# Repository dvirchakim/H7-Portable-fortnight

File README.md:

# Flight-controller carrier for Arduino® Portenta H7

**A 68 × 40 mm, 4-layer carrier that snaps onto the Portenta H7's two high-density connectors and turns it
into an ArduPilot-class flight controller**, with Pixhawk-standard ports, microSD logging and DroneCAN.

**Revision R0.4 · fab-ready, not yet built.** DRC and ERC clean, 0 JLCDFM-style dangers, schematic and PCB
agree pad for pad, sockets match Arduino's own Portenta Breakout to 0.000 mm.

## Highlights

- **Power:** 3–6S LiPo in, TI LMR33630 buck, 5.25 V at 2 A continuous (1.5 A from 3S), 3 A peaks.
- **Sensors:** TDK ICM-45686 IMU at the board centre, Bosch BMP581 barometer shielded under the module.
- **Logging and buses:** 4-bit microSD, DroneCAN (terminated by default), I2C.
- **Ports:** GPS, TELEM (with flow control), RC, UART, CAN and I2C on JST-GH with Pixhawk DS-009
  pinouts; 4-in-1 ESC on JST-SH 8 in the Betaflight standard order.
- **Motors:** DShot and bidirectional DShot on all four; ESC telemetry on its own UART.
- **Measurement:** battery voltage and ESC current into an ADC with its own 2.5 V reference.
- **Mounting:** 30.5 mm M3 stack pattern; the module is held by its own four M2 holes.
- **Built from code:** everything is generated from one Python netlist (`scripts/design.py`) and
  checked by scripts: DRC, ERC, DFM, EMI, socket match, JLCPCB placement.

## Specifications

| | |
|---|---|
| Board | 68 × 40 mm, 4 layers (GND and 5 V planes), 1.6 mm, black mask / white silk, ENIG |
| Module | Portenta H7 / H7 Lite (STM32H747, M7 480 MHz + M4) on two Hirose DF40HC(3.5), 3.5 mm stack |
| Input | 3–6S LiPo through solder pads or the ESC harness; SMBJ26A TVS |
| Outputs | M1–M4 (DShot), S5, S6, WS2812 LED strip, buzzer |
| Parts | 63 placed parts, 32 BOM lines; about $22 per board in parts at 10 boards (module not included) |
| Assembly | JLCPCB, both sides; the DF40 sockets are consigned |

## Architecture

| Block | Parts | H7 signals |
|---|---|---|
| Power | 3-6S VBAT -> TVS -> LMR33630 buck 5.25 V (2 A continuous from 4-6S, ~1.5 A from 3S, 3 A peaks) -> SS34 -> +5V -> H7 VIN | J1-21/32/41/48 |
| Sensor rail | LP5907 3.3 V low-noise LDO from +5V | — |
| IMU | TDK ICM-45686, SPI | SPI1 CK/CIPO/COPI (PI1/PC2/PC3), CS PI0, INT GPIO2 (PD4) |
| Barometer | Bosch BMP581 (I2C, address 0x46) | I2C0 (PH8/PH7 = I2C3) |
| Magnetometer | LIS3MDL footprint, not fitted — use the GPS module's compass | I2C0 |
| Motors M1-M4 | 8-pin JST-SH 4-in-1 ESC connector (Betaflight standard order) | M1 PWM5 PK1 TIM1_CH1, M2 PWM4 PJ11 TIM1_CH2, M3 PWM1 PC6 TIM3_CH1, M4 PWM2 PC7 TIM3_CH2: no complementary channels, DMA on both timers, so DShot and bidirectional DShot work on all four |
| Aux S5, S6, LED strip | pads | LED strip PWM8 PJ10 = TIM8_CH2 (has DMA, so WS2812 works); S6 PWM6 PH15 = TIM8_CH3N (shares TIM8 with the LEDs: second LED string or GPIO while they run); S5 PWM9 PH6 = TIM12_CH1 (servo PWM) |
| Buzzer | 2N7002 low-side switch (R13 100k), pad | PWM7 PJ7 as a GPIO: active buzzer |
| Status / power LEDs | red (GPIO3) / white (+5V) | GPIO3 PD5 |
| Battery sense | VBAT 11:1 divider -> A6; ESC current (10k + 100 nF) -> A7; ADC VREF+ = 2.5 V from a TI REF3125 (U7) | A6 PA4 J2-78, A7 PA6 J2-80, VREF+ J2-71 (VREF- J2-72 to GND) |
| GPS + compass | JST-GH 6 (5V TX RX SCL SDA GND) | UART0 + I2C0 |
| Telemetry | JST-GH 6 with RTS/CTS | UART1 (USART1) |
| RC receiver | JST-GH 4 | UART2 (USART6) |
| Spare UART | JST-GH 4 | UART3 (UART8) |
| ESC telemetry | J10 pin 4 | PA8 = UART7_RX (J2-59), its own UART (the module's Bluetooth UART: keep Bluetooth off) |
| CAN | SN65HVD230 + JST-GH 4; 120 ohm terminator ON by default (bridged JP1: cut to remove) | CAN1 TX/RX (PH13/PB8) = FDCAN1 |
| I2C expansion | JST-GH 4 | I2C0 |
| microSD | Molex 104031-0811 | SDC (SDMMC2) |
| Debug | SWDIO/SWCLK/NRST/GND/3V3 pads (bottom) | J1-75/77/73 |

The +5V rail sits after the Schottky, on the same node as the H7's VIN, so the sensors and ports
run from USB on the bench and USB cannot back-feed the buck.

## Snap-on interface

- Carrier sockets J1/J2: **Hirose DF40HC(3.5)-80DS-0.4V(51)**, mating the H7's DF40C-80DP-0.4V(51).
  Board-to-board gap 3.5 mm.
- J1/J2 are 43.18 mm apart on the H7 centreline (17.14 mm and 60.32 mm from the USB edge).
- Pin 1, seen from the top with USB on the left: J1 pin 1 is in the USB-side row at the lower end;
  J2 pin 1 is in the outer row at the upper end. Same as Arduino's Portenta Breakout
  (`scripts/check_sockets.py`).
- Four M2 holes line up with the H7's corner holes — use 3.5 mm spacers so vibration is not
  carried by the connectors. At the J2 end use round spacers of 3 mm diameter or less.
- Four M3 holes on the standard 30.5 x 30.5 mm stack pattern.
- Under the H7 the top side carries only low parts (LGA sensors, 0402). Everything tall (buck,
  inductor, microSD, CAN transceiver) is on the bottom.

## Documentation

| Topic | What's there |
|---|---|
| [Rev 0.4 changes](docs/rev-0.4/README.md) | Sensor cost pass: BMP581 barometer; IMU options checked |
| [Rev 0.3 changes](docs/rev-0.3/README.md) | The design review: what was found and fixed, what's left for rev 0.4 |
| [Rev 0.2 changes](docs/rev-0.2/README.md) | Re-route, buck loop, EMI ring, cost pass, sensor swap |
| [Verification](docs/verification/README.md) | The "must verify before ordering" checks with results, and the bring-up / production test |
| [Ordering](docs/ordering/README.md) | What to upload to JLCPCB, stackup, consigning the DF40 sockets |
| [BOM and cost](docs/bom-and-cost/README.md) | Cost per board and why each main part was chosen |
| [Placement check](docs/placement-check/README.md) | JLCPCB footprint corrections and what they caught |
| [DFM](docs/dfm/README.md) | JLCDFM-style manufacturability results |
| [EMI](docs/emi/README.md) | Layout checks and the bench test procedure |
| [Routing](docs/routing/README.md) | Layer stack and the routing flow |
| [Silkscreen](docs/silkscreen/README.md) | Labels, forward arrows, QR code |
| [Firmware](docs/firmware/README.md) | The ArduPilot port: what the board definition needs |
| [Design review page](docs/FC_Carrier_R0.3_review.html) | The rev 0.3 review written for an Arduino Pro pitch |

## Repository layout

| File | What |
|---|---|
| `portenta_drone_fc.kicad_pro` | Open this in KiCad 7 |
| `portenta_drone_fc.kicad_sch` | Schematic (net-label style, one sheet) |
| `portenta_drone_fc.kicad_pcb` | Routed 4-layer board |
| `fc.pretty/`, `fc.kicad_sym` | Project footprint (DF40 socket) and symbols |
| `bom_placement.csv` | Parts, MPNs, side and XY (from `design.py`) |
| `fab/` | Gerber zip, JLCPCB BOM and CPL, `bom_cost.csv`, `placement_check.csv` |
| `out/` | Renders, `drc.rpt`, `dfm.rpt`, `emi.rpt` |
| `docs/` | One folder per topic (see Documentation above), the 3D renders, `portenta_breakout_sockets.json` (Arduino's socket pads) and `FC_Carrier_R0.3_review.html` (the rev 0.3 design review for the Arduino pitch) |
| `scripts/design.py` | **Single source of truth** — parts, nets, placement |
| `scripts/regen_docs.py` | Rewrites schematic + BOM CSV from `design.py` without touching the routed board |
| `scripts/check_sockets.py` | Compares J1/J2 pad by pad with Arduino's Portenta Breakout and Hirose's land pattern / hatched area (exit 0 = match) |
| `scripts/erc.py` | ERC for the generated schematic plus schematic-vs-PCB parity, pad by pad (exit 0 = clean) |
| `scripts/power_copper.py` | Thermal vias in U1's exposed pad and power tracks widened as far as clearance allows |
| `scripts/render3d/` | Headless 3D renders of the board (STEP export -> blocks, layer textures, Blender) |
| `scripts/r03_renet.py`, `scripts/r03_rip.py` | The rev 0.3 review changes as applied to the routed board: net swaps, pad re-assignments, new footprints, then removal of the obsolete copper (run once; kept as the record) |
| `scripts/altium_pads.py` | Reads pads/nets from an Altium `.PcbDoc` with plain Python (made the reference JSON) |

`scripts/gen.py --force` would regenerate the board and discard the routing — do not use it now.

---

Arduino® and Portenta are trademarks of Arduino S.r.l. / Arduino SA. This is an independent design, not an
Arduino product.

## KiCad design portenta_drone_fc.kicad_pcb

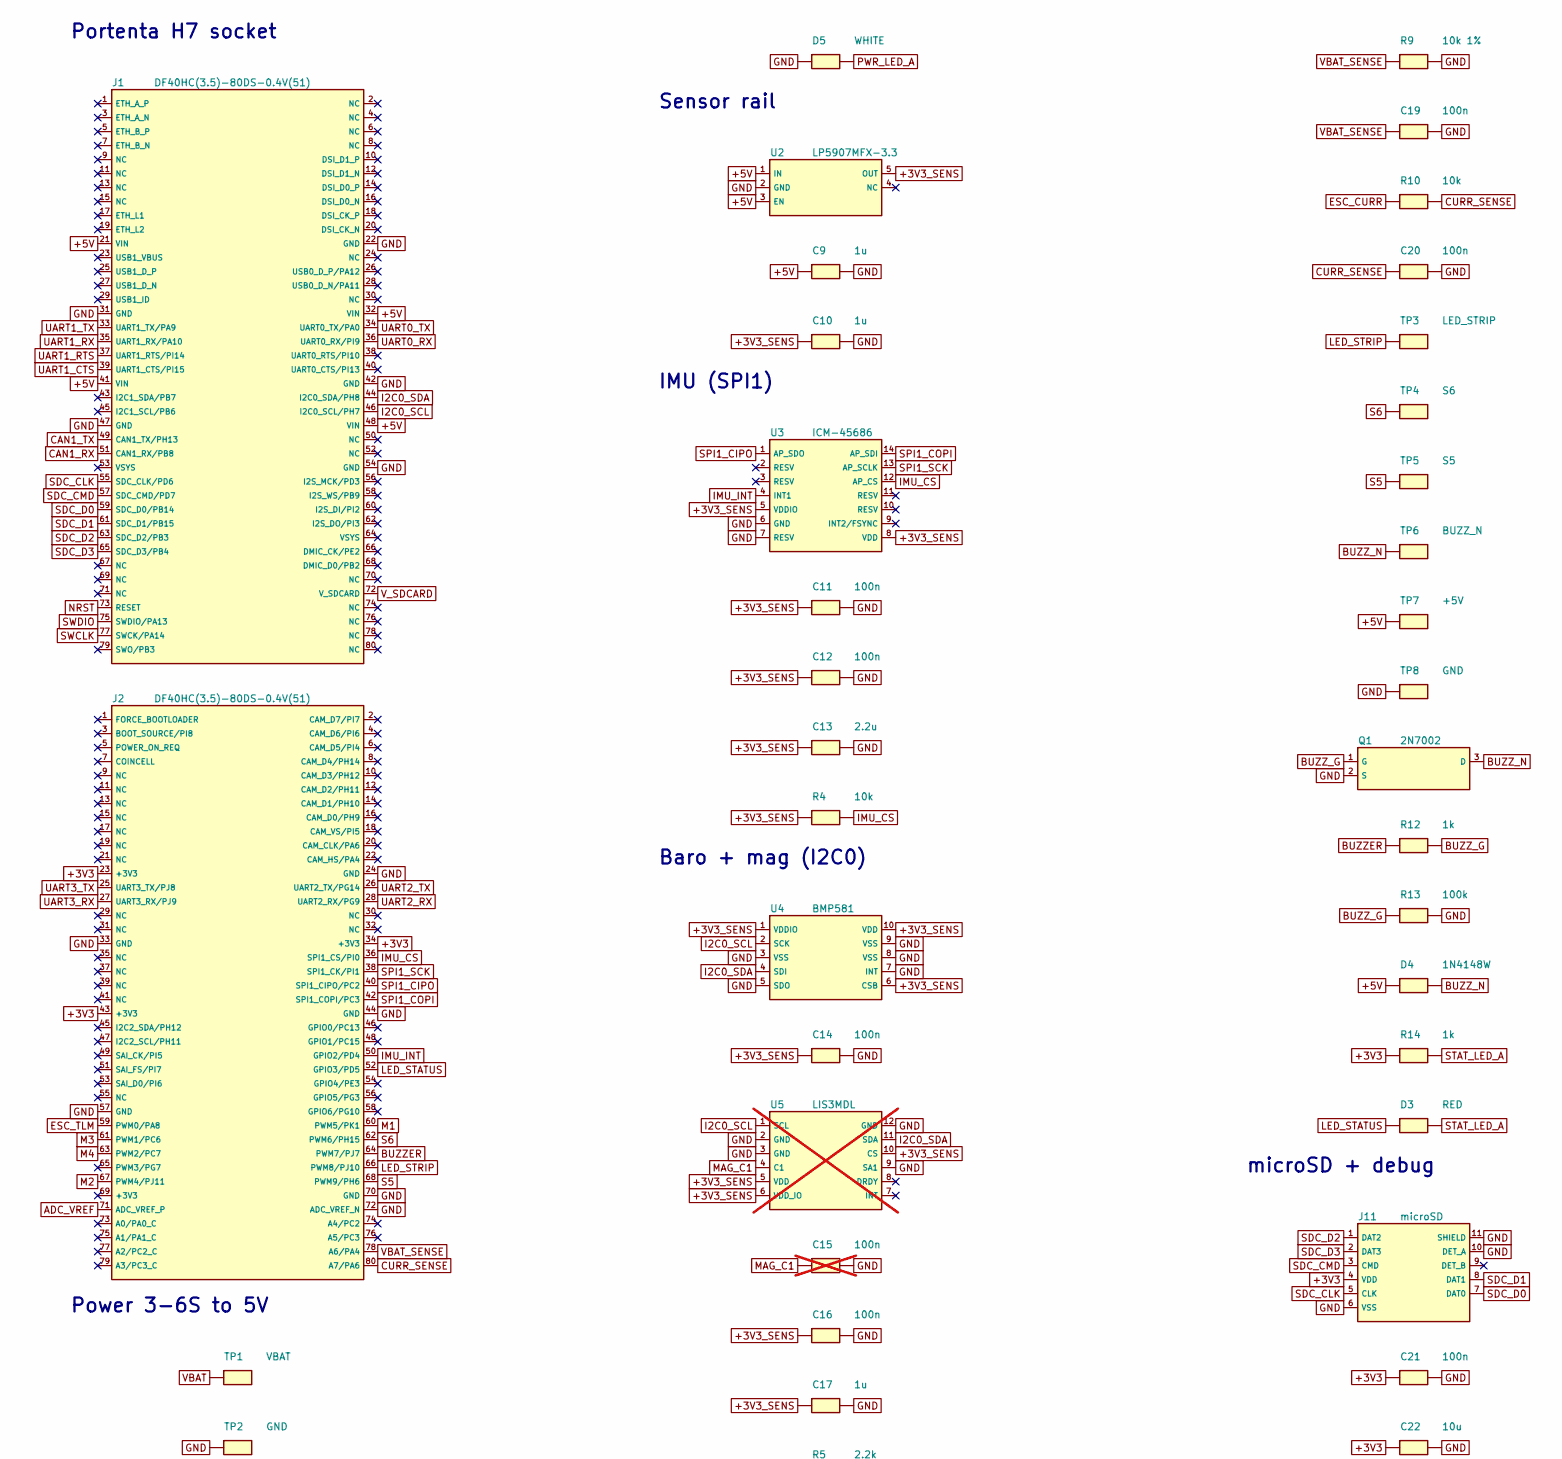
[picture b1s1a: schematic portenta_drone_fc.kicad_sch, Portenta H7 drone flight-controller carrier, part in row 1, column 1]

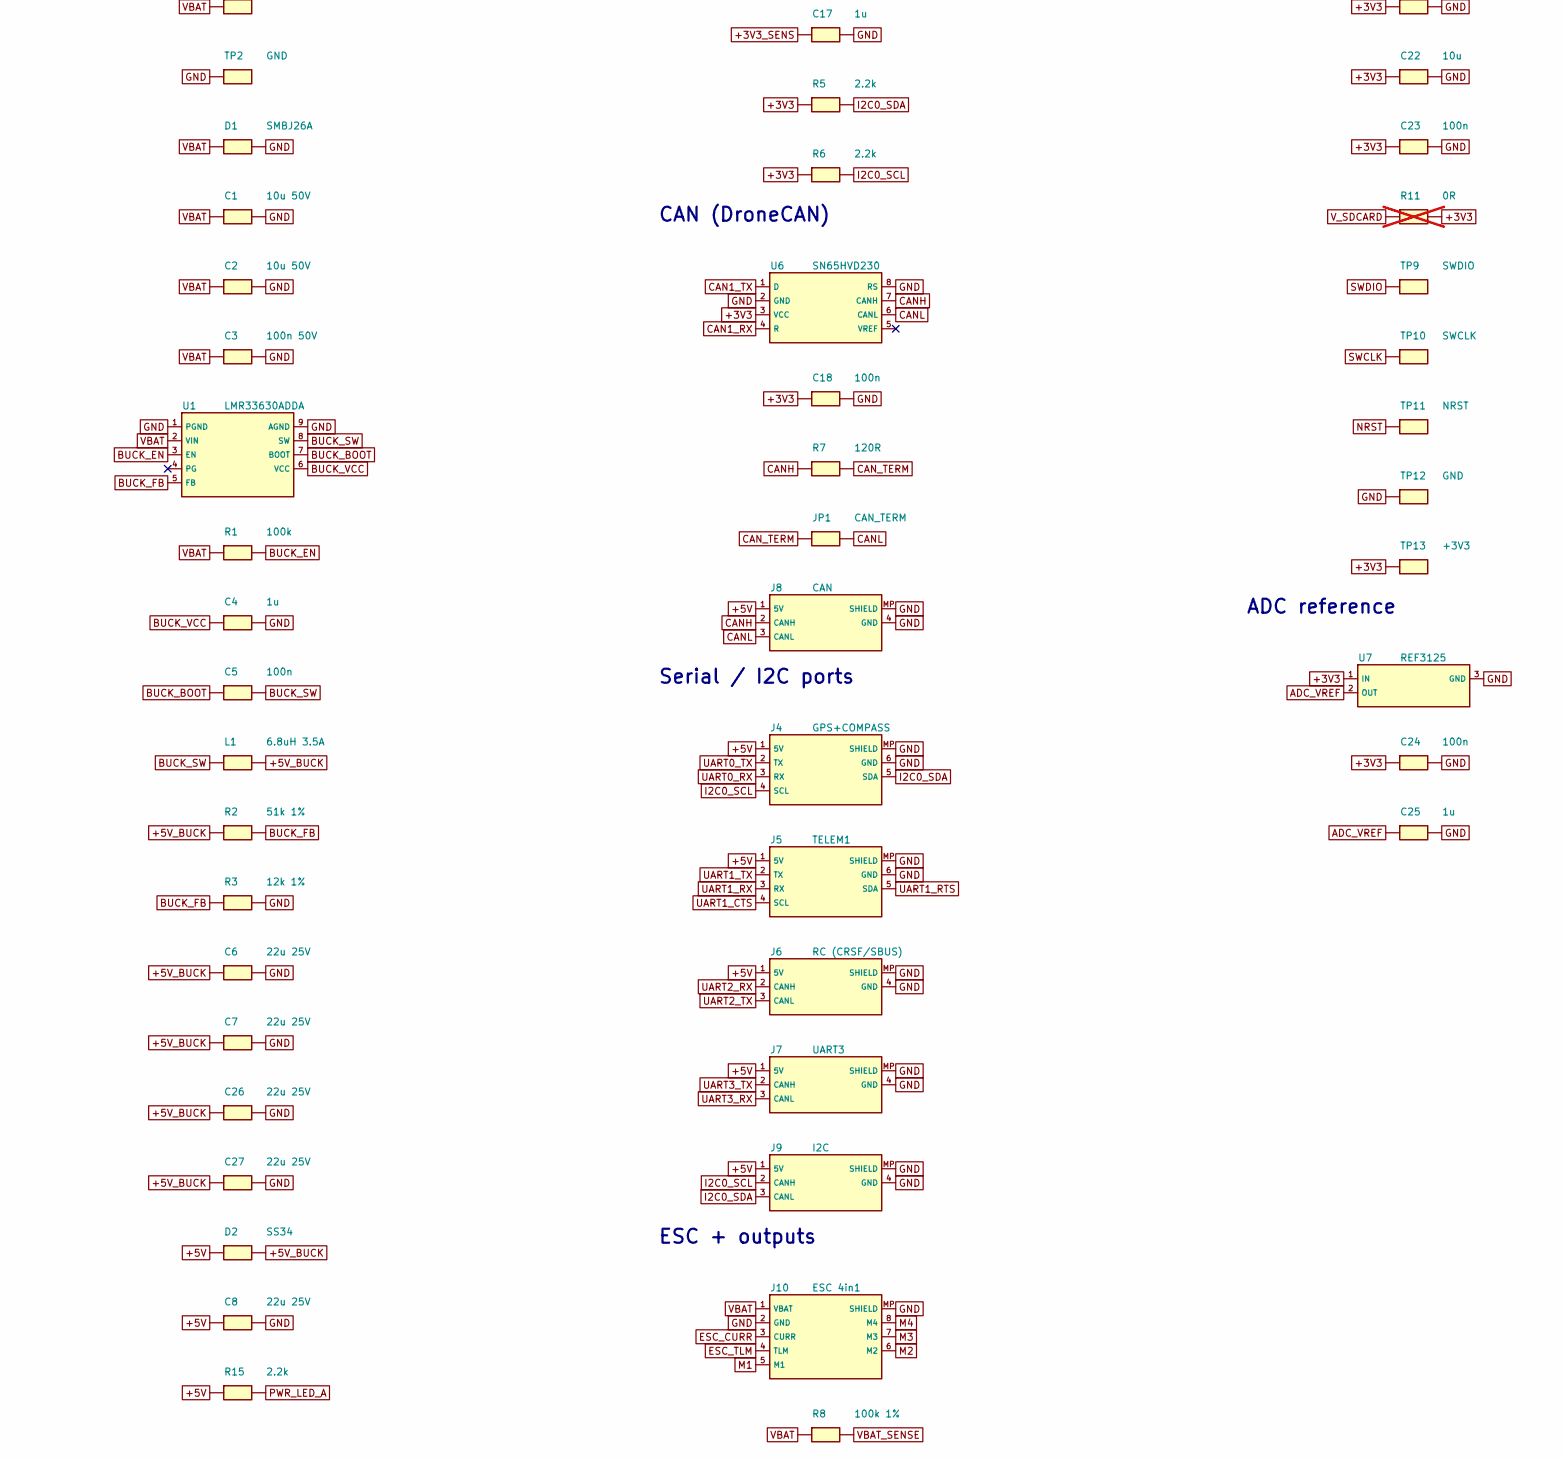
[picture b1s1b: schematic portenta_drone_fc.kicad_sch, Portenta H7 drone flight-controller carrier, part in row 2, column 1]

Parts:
C1, C2: 10u 50V; C_1206_3216Metric
C3: 100n 50V; C_0603_1608Metric
C4, C9, C10, C17, C25: 1u; C_0402_1005Metric
C5, C11, C12, C14, C16, C18, C19, C20, C21, C23, C24: 100n; C_0402_1005Metric
C6, C7, C8, C26, C27: 22u 25V; C_0805_2012Metric
C13: 2.2u; C_0402_1005Metric
C15: 100n; C_0402_1005Metric; not fitted
C22: 10u; C_0805_2012Metric
D1: SMBJ26A; D_SMB; MPN SMBJ26A
D2: SS34; D_SMA; MPN SS34
D3: RED; LED_0603_1608Metric
D4: 1N4148W; D_SOD-123; MPN 1N4148W
D5: WHITE; LED_0603_1608Metric
J1, J2: DF40HC(3.5)-80DS-0.4V(51); Hirose_DF40HC(3.5)-80DS-0.4V_2x40_P0.4mm; MPN DF40HC(3.5)-80DS-0.4V(51)
J4: GPS+COMPASS; JST_GH_SM06B-GHS-TB_1x06-1MP_P1.25mm_Horizontal
J5: TELEM1; JST_GH_SM06B-GHS-TB_1x06-1MP_P1.25mm_Horizontal
J6: RC (CRSF/SBUS); JST_GH_SM04B-GHS-TB_1x04-1MP_P1.25mm_Horizontal
J7: UART3; JST_GH_SM04B-GHS-TB_1x04-1MP_P1.25mm_Horizontal
J8: CAN; JST_GH_SM04B-GHS-TB_1x04-1MP_P1.25mm_Horizontal
J9: I2C; JST_GH_SM04B-GHS-TB_1x04-1MP_P1.25mm_Horizontal
J10: ESC 4in1; JST_SH_SM08B-SRSS-TB_1x08-1MP_P1.00mm_Horizontal
J11: microSD; microSD_HC_Molex_104031-0811; MPN 104031-0811
JP1: CAN_TERM; SolderJumper-2_P1.3mm_Bridged_RoundedPad1.0x1.5mm
L1: 6.8uH 3.5A; L_Bourns_SRP5030T; MPN MDA5030-6R8M
Q1: 2N7002; SOT-23; MPN 2N7002
R1, R13: 100k; R_0402_1005Metric
R2: 51k 1%; R_0402_1005Metric
R3: 12k 1%; R_0402_1005Metric
R4, R10: 10k; R_0402_1005Metric
R5, R6, R15: 2.2k; R_0402_1005Metric
R7: 120R; R_0402_1005Metric
R8: 100k 1%; R_0402_1005Metric
R9: 10k 1%; R_0402_1005Metric
R11: 0R; R_0402_1005Metric; not fitted
R12, R14: 1k; R_0402_1005Metric
TP1: VBAT; TestPoint_Pad_3.0x3.0mm
TP2: GND; TestPoint_Pad_3.0x3.0mm
TP3: LED_STRIP; TestPoint_Pad_1.5x1.5mm
TP4: S6; TestPoint_Pad_1.5x1.5mm
TP5: S5; TestPoint_Pad_1.5x1.5mm
TP6: BUZZ_N; TestPoint_Pad_1.5x1.5mm
TP7: +5V; TestPoint_Pad_1.5x1.5mm
TP8: GND; TestPoint_Pad_1.5x1.5mm
TP9: SWDIO; TestPoint_Pad_D1.5mm
TP10: SWCLK; TestPoint_Pad_D1.5mm
TP11: NRST; TestPoint_Pad_D1.5mm
TP12: GND; TestPoint_Pad_D1.5mm
TP13: +3V3; TestPoint_Pad_D1.5mm
U1: LMR33630ADDA; Texas_HSOP-8-1EP_3.9x4.9mm_P1.27mm; MPN LMR33630ADDAR
U2: LP5907MFX-3.3; SOT-23-5; MPN LP5907MFX-3.3/NOPB
U3: ICM-45686; LGA-14_3x2.5mm_P0.5mm_LayoutBorder3x4y; MPN ICM-45686
U4: BMP581; Bosch_LGA-10_2x2mm_P0.5mm_BMP581; MPN BMP581
U5: LIS3MDL; LGA-12_2x2mm_P0.5mm; MPN LIS3MDLTR; not fitted
U6: SN65HVD230; SOIC-8_3.9x4.9mm_P1.27mm; MPN SN65HVD230DR
U7: REF3125; SOT-23; MPN REF3125AIDBZR

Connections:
+3V3: C18.1, C21.1, C22.1, C23.1, C24.1, J2.23 (+3V3), J2.34 (+3V3), J2.43 (+3V3), J11.4 (VDD), R5.1, R6.1, R11.2, R14.1, TP13.1, U6.3 (VCC), U7.1 (IN)
+3V3_SENS: C10.1, C11.1, C12.1, C13.1, C14.1, C16.1, C17.1, R4.1, U2.5 (OUT), U3.5 (VDDIO), U3.8 (VDD), U4.1 (VDDIO), U4.6 (CSB), U4.10 (VDD), U5.5 (VDD), U5.6 (VDD_IO), U5.10 (CS)
+5V: C8.1, C9.1, D2.1 (K), D4.1 (K), J1.21 (VIN), J1.32 (VIN), J1.41 (VIN), J1.48 (VIN), J4.1 (5V), J5.1 (5V), J6.1 (5V), J7.1 (5V), J8.1 (5V), J9.1 (5V), R15.1, TP7.1, U2.1 (IN), U2.3 (EN)
+5V_BUCK: C6.1, C7.1, C26.1, C27.1, D2.2 (A), L1.2, R2.1
ADC_VREF: C25.1, J2.71 (ADC_VREF_P), U7.2 (OUT)
BUCK_BOOT: C5.1, U1.7 (BOOT)
BUCK_EN: R1.2, U1.3 (EN)
BUCK_FB: R2.2, R3.1, U1.5 (FB)
BUCK_SW: C5.2, L1.1, U1.8 (SW)
BUCK_VCC: C4.1, U1.6 (VCC)
BUZZER: J2.64 (PWM7/PJ7), R12.1
BUZZ_G: Q1.1 (G), R12.2, R13.1
BUZZ_N: D4.2 (A), Q1.3 (D), TP6.1
CAN1_RX: J1.51 (CAN1_RX/PB8), U6.4 (R)
CAN1_TX: J1.49 (CAN1_TX/PH13), U6.1 (D)
CANH: J8.2 (CANH), R7.1, U6.7 (CANH)
CANL: J8.3 (CANL), JP1.2, U6.6 (CANL)
CAN_TERM: JP1.1, R7.2
CURR_SENSE: C20.1, J2.80 (A7/PA6), R10.2
ESC_CURR: J10.3 (CURR), R10.1
ESC_TLM: J2.59 (PWM0/PA8), J10.4 (TLM)
GND: C1.2, C2.2, C3.2, C4.2, C6.2, C7.2, C8.2, C9.2, C10.2, C11.2, C12.2, C13.2, C14.2, C15.2, C16.2, C17.2, C18.2, C19.2, C20.2, C21.2, C22.2, C23.2, C24.2, C25.2, C26.2, C27.2, D1.2 (A), D5.1 (K), J1.22 (GND), J1.31 (GND), J1.42 (GND), J1.47 (GND), J1.54 (GND), J2.24 (GND), J2.33 (GND), J2.44 (GND), J2.57 (GND), J2.70 (GND), J2.72 (ADC_VREF_N), J4.6 (GND), J4.MP (SHIELD), J5.6 (GND), J5.MP (SHIELD), J6.4 (GND), J6.MP (SHIELD), J7.4 (GND), J7.MP (SHIELD), J8.4 (GND), J8.MP (SHIELD), J9.4 (GND), J9.MP (SHIELD), J10.2 (GND), J10.MP (SHIELD), J11.6 (VSS), J11.10 (DET_A), J11.11 (SHIELD), Q1.2 (S), R3.2, R9.2, R13.2, TP2.1, TP8.1, TP12.1, U1.1 (PGND), U1.9 (AGND), U2.2 (GND), U3.6 (GND), U3.7 (RESV), U4.3 (VSS), U4.5 (SDO), U4.7 (INT), U4.8 (VSS), U4.9 (VSS), U5.2 (GND), U5.3 (GND), U5.9 (SA1), U5.12 (GND), U6.2 (GND), U6.8 (RS), U7.3 (GND)
I2C0_SCL: J1.46 (I2C0_SCL/PH7), J4.4 (SCL), J9.2 (CANH), R6.2, U4.2 (SCK), U5.1 (SCL)
I2C0_SDA: J1.44 (I2C0_SDA/PH8), J4.5 (SDA), J9.3 (CANL), R5.2, U4.4 (SDI), U5.11 (SDA)
IMU_CS: J2.36 (SPI1_CS/PI0), R4.2, U3.12 (AP_CS)
IMU_INT: J2.50 (GPIO2/PD4), U3.4 (INT1)
LED_STATUS: D3.1 (K), J2.52 (GPIO3/PD5)
LED_STRIP: J2.66 (PWM8/PJ10), TP3.1
M1: J2.60 (PWM5/PK1), J10.5 (M1)
M2: J2.67 (PWM4/PJ11), J10.6 (M2)
M3: J2.61 (PWM1/PC6), J10.7 (M3)
M4: J2.63 (PWM2/PC7), J10.8 (M4)
MAG_C1: C15.1, U5.4 (C1)
NRST: J1.73 (RESET), TP11.1
PWR_LED_A: D5.2 (A), R15.2
S5: J2.68 (PWM9/PH6), TP5.1
S6: J2.62 (PWM6/PH15), TP4.1
SDC_CLK: J1.55 (SDC_CLK/PD6), J11.5 (CLK)
SDC_CMD: J1.57 (SDC_CMD/PD7), J11.3 (CMD)
SDC_D0: J1.59 (SDC_D0/PB14), J11.7 (DAT0)
SDC_D1: J1.61 (SDC_D1/PB15), J11.8 (DAT1)
SDC_D2: J1.63 (SDC_D2/PB3), J11.1 (DAT2)
SDC_D3: J1.65 (SDC_D3/PB4), J11.2 (DAT3)
SPI1_CIPO: J2.40 (SPI1_CIPO/PC2), U3.1 (AP_SDO)
SPI1_COPI: J2.42 (SPI1_COPI/PC3), U3.14 (AP_SDI)
SPI1_SCK: J2.38 (SPI1_CK/PI1), U3.13 (AP_SCLK)
STAT_LED_A: D3.2 (A), R14.2
SWCLK: J1.77 (SWCK/PA14), TP10.1
SWDIO: J1.75 (SWDIO/PA13), TP9.1
UART0_RX: J1.36 (UART0_RX/PI9), J4.3 (RX)
UART0_TX: J1.34 (UART0_TX/PA0), J4.2 (TX)
UART1_CTS: J1.39 (UART1_CTS/PI15), J5.4 (SCL)
UART1_RTS: J1.37 (UART1_RTS/PI14), J5.5 (SDA)
UART1_RX: J1.35 (UART1_RX/PA10), J5.3 (RX)
UART1_TX: J1.33 (UART1_TX/PA9), J5.2 (TX)
UART2_RX: J2.28 (UART2_RX/PG9), J6.2 (CANH)
UART2_TX: J2.26 (UART2_TX/PG14), J6.3 (CANL)
UART3_RX: J2.27 (UART3_RX/PJ9), J7.3 (CANL)
UART3_TX: J2.25 (UART3_TX/PJ8), J7.2 (CANH)
VBAT: C1.1, C2.1, C3.1, D1.1 (K), J10.1 (VBAT), R1.1, R8.1, TP1.1, U1.2 (VIN)
VBAT_SENSE: C19.1, J2.78 (A6/PA4), R8.2, R9.1
V_SDCARD: J1.72 (V_SDCARD), R11.1

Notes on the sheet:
Portenta H7 socket
Power 3-6S to 5V
Sensor rail
IMU (SPI1)
Baro + mag (I2C0)
CAN (DroneCAN)
Serial / I2C ports
ESC + outputs
microSD + debug
ADC reference

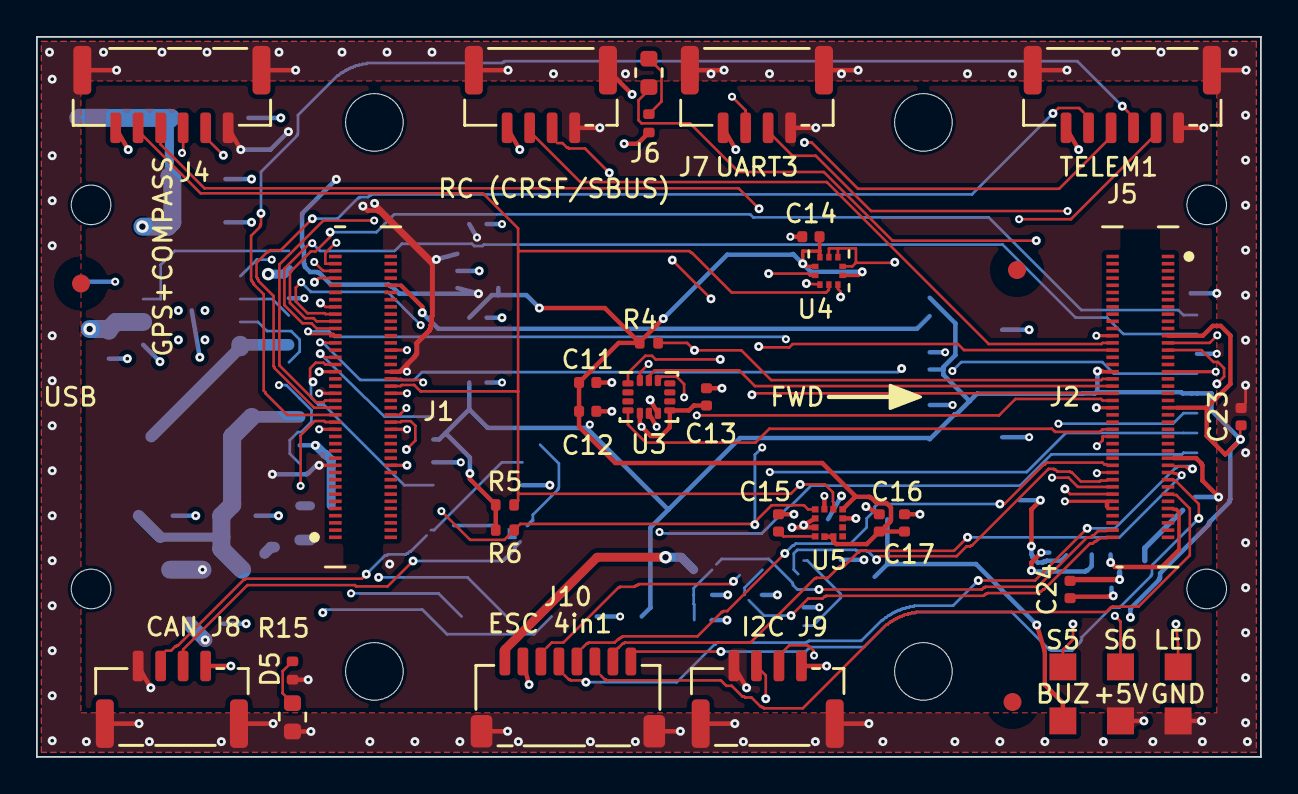
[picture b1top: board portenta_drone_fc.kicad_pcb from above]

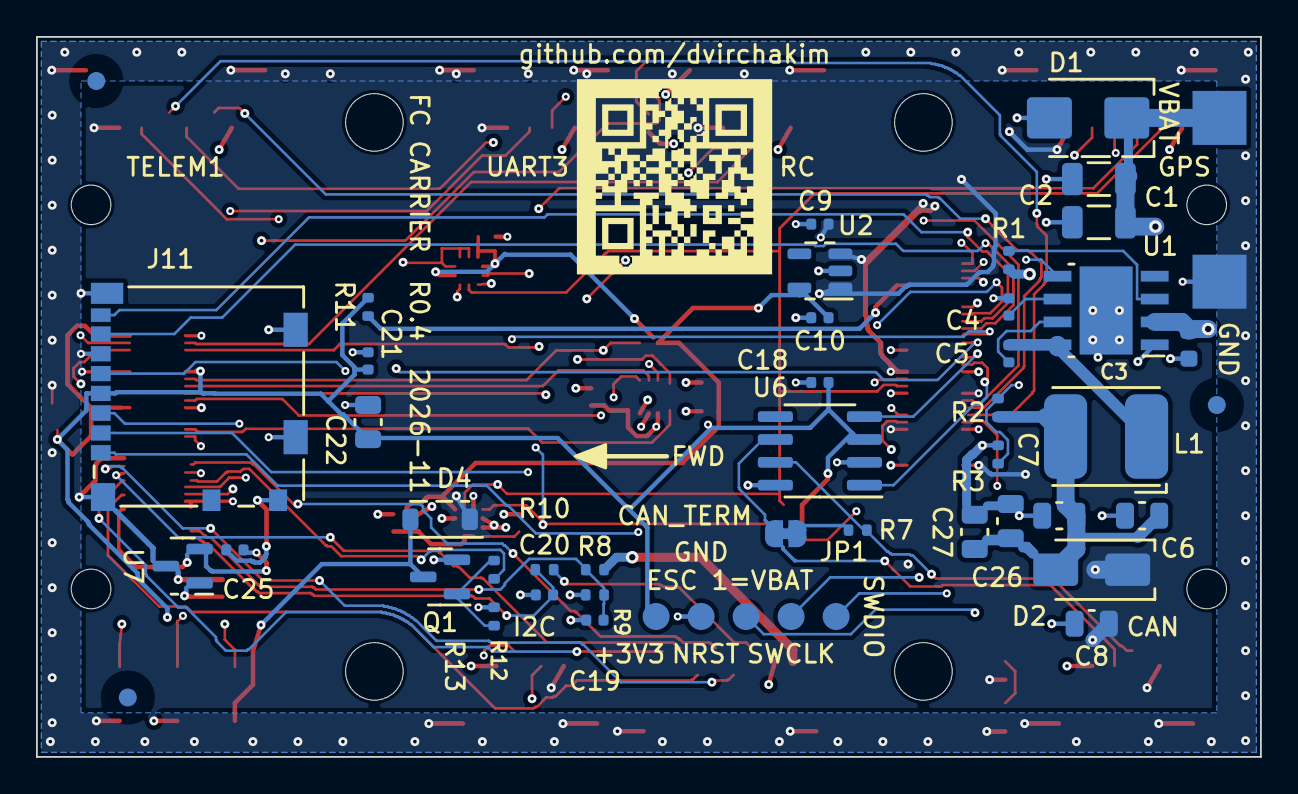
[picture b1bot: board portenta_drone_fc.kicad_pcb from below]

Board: 4 copper layers, 68.0 x 40.0 mm, 94 parts (49 on the bottom side), 62 nets.

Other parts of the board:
FID1, FID2, FID3, FID4, FID5, FID6: Fiducial; Fiducial_1mm_Mask2mm
H1, H2, H3, H4: M3 30.5mm stack; MountingHole_3.2mm_M3
H5, H6, H7, H8: M2 Portenta standoff; MountingHole_2.2mm_M2

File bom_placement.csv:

Ref,Value,MPN,Footprint,Side,X_mm,Y_mm,Rot
J1,DF40HC(3.5)-80DS-0.4V(51),DF40HC(3.5)-80DS-0.4V(51),fc:Hirose_DF40HC(3.5)-80DS-0.4V_2x40_P0.4mm,F,18.12,20.00,0
J2,DF40HC(3.5)-80DS-0.4V(51),DF40HC(3.5)-80DS-0.4V(51),fc:Hirose_DF40HC(3.5)-80DS-0.4V_2x40_P0.4mm,F,61.30,20.00,180
TP1,VBAT,,TestPoint:TestPoint_Pad_3.0x3.0mm,B,2.30,4.50,0
TP2,GND,,TestPoint:TestPoint_Pad_3.0x3.0mm,B,2.30,13.60,0
D1,SMBJ26A,SMBJ26A,Diode_SMD:D_SMB,B,9.60,4.50,0
C1,10u 50V,,Capacitor_SMD:C_1206_3216Metric,B,9.00,7.90,0
C2,10u 50V,,Capacitor_SMD:C_1206_3216Metric,B,9.00,10.30,0
C3,100n 50V,,Capacitor_SMD:C_0603_1608Metric,B,4.00,17.10,270
U1,LMR33630ADDA,LMR33630ADDAR,Package_SO:Texas_HSOP-8-1EP_3.9x4.9mm_P1.27mm,B,8.60,15.20,0
R1,100k,,Resistor_SMD:R_0402_1005Metric,B,14.00,12.40,90
C4,1u,,Capacitor_SMD:C_0402_1005Metric,B,14.00,15.00,90
C5,100n,,Capacitor_SMD:C_0402_1005Metric,B,14.00,17.60,90
L1,6.8uH 3.5A,MDA5030-6R8M,Inductor_SMD:L_Bourns_SRP5030T,B,8.60,22.20,0
R2,51k 1%,,Resistor_SMD:R_0402_1005Metric,B,14.60,20.60,90
R3,12k 1%,,Resistor_SMD:R_0402_1005Metric,B,14.60,23.20,90
C6,22u 25V,,Capacitor_SMD:C_0805_2012Metric,B,6.60,26.60,0
C7,22u 25V,,Capacitor_SMD:C_0805_2012Metric,B,11.20,26.60,0
C26,22u 25V,,Capacitor_SMD:C_0805_2012Metric,B,13.90,26.90,90
C27,22u 25V,,Capacitor_SMD:C_0805_2012Metric,B,15.90,27.50,90
D2,SS34,SS34,Diode_SMD:D_SMA,B,9.40,29.60,0
C8,22u 25V,,Capacitor_SMD:C_0805_2012Metric,B,9.40,32.60,0
R15,2.2k,,Resistor_SMD:R_0402_1005Metric,F,14.20,35.20,90
D5,WHITE,,LED_SMD:LED_0603_1608Metric,F,14.20,37.80,90
U2,LP5907MFX-3.3,LP5907MFX-3.3/NOPB,Package_TO_SOT_SMD:SOT-23-5,B,24.50,13.00,0
C9,1u,,Capacitor_SMD:C_0402_1005Metric,B,24.50,10.40,0
C10,1u,,Capacitor_SMD:C_0402_1005Metric,B,24.50,15.60,0
U3,ICM-45686,ICM-45686,Package_LGA:LGA-14_3x2.5mm_P0.5mm_LayoutBorder3x4y,F,34.00,20.00,0
C11,100n,,Capacitor_SMD:C_0402_1005Metric,F,30.60,19.20,0
C12,100n,,Capacitor_SMD:C_0402_1005Metric,F,30.60,20.80,0
C13,2.2u,,Capacitor_SMD:C_0402_1005Metric,F,37.20,20.00,90
R4,10k,,Resistor_SMD:R_0402_1005Metric,F,34.00,17.00,0
U4,BMP581,BMP581,fc:Bosch_LGA-10_2x2mm_P0.5mm_BMP581,F,44.00,13.00,0
C14,100n,,Capacitor_SMD:C_0402_1005Metric,F,43.00,11.10,180
U5,LIS3MDL,LIS3MDLTR,Package_LGA:LGA-12_2x2mm_P0.5mm,F,44.00,27.00,0
C15,100n,,Capacitor_SMD:C_0402_1005Metric,F,41.20,27.00,90
C16,100n,,Capacitor_SMD:C_0402_1005Metric,F,46.80,27.00,90
C17,1u,,Capacitor_SMD:C_0402_1005Metric,F,48.20,27.00,90
R5,2.2k,,Resistor_SMD:R_0402_1005Metric,F,26.00,26.00,0
R6,2.2k,,Resistor_SMD:R_0402_1005Metric,F,26.00,27.40,0
U6,SN65HVD230,SN65HVD230DR,Package_SO:SOIC-8_3.9x4.9mm_P1.27mm,B,24.50,23.00,0
C18,100n,,Capacitor_SMD:C_0402_1005Metric,B,24.50,19.20,0
R7,120R,,Resistor_SMD:R_0402_1005Metric,B,22.40,27.40,0
JP1,CAN_TERM,,Jumper:SolderJumper-2_P1.3mm_Bridged_RoundedPad1.0x1.5mm,B,26.40,27.60,0
J8,CAN,,Connector_JST:JST_GH_SM04B-GHS-TB_1x04-1MP_P1.25mm_Horizontal,F,7.50,36.80,0
J4,GPS+COMPASS,,Connector_JST:JST_GH_SM06B-GHS-TB_1x06-1MP_P1.25mm_Horizontal,F,7.50,3.20,180
J5,TELEM1,,Connector_JST:JST_GH_SM06B-GHS-TB_1x06-1MP_P1.25mm_Horizontal,F,60.30,3.20,180
J6,RC (CRSF/SBUS),,Connector_JST:JST_GH_SM04B-GHS-TB_1x04-1MP_P1.25mm_Horizontal,F,28.00,3.20,180
J7,UART3,,Connector_JST:JST_GH_SM04B-GHS-TB_1x04-1MP_P1.25mm_Horizontal,F,40.00,3.20,180
J9,I2C,,Connector_JST:JST_GH_SM04B-GHS-TB_1x04-1MP_P1.25mm_Horizontal,F,40.60,36.80,0
J10,ESC 4in1,,Connector_JST:JST_SH_SM08B-SRSS-TB_1x08-1MP_P1.00mm_Horizontal,F,29.50,36.70,0
R8,100k 1%,,Resistor_SMD:R_0402_1005Metric,B,37.00,29.60,0
R9,10k 1%,,Resistor_SMD:R_0402_1005Metric,B,37.00,31.00,0
C19,100n,,Capacitor_SMD:C_0402_1005Metric,B,37.00,32.40,0
R10,10k,,Resistor_SMD:R_0402_1005Metric,B,39.80,29.60,0
C20,100n,,Capacitor_SMD:C_0402_1005Metric,B,39.80,31.00,0
TP3,LED_STRIP,,TestPoint:TestPoint_Pad_1.5x1.5mm,F,57.00,35.00,0
TP4,S6,,TestPoint:TestPoint_Pad_1.5x1.5mm,F,60.20,35.00,0
TP5,S5,,TestPoint:TestPoint_Pad_1.5x1.5mm,F,63.40,35.00,0
TP6,BUZZ_N,,TestPoint:TestPoint_Pad_1.5x1.5mm,F,57.00,38.00,0
TP7,+5V,,TestPoint:TestPoint_Pad_1.5x1.5mm,F,60.20,38.00,0
TP8,GND,,TestPoint:TestPoint_Pad_1.5x1.5mm,F,63.40,38.00,0
Q1,2N7002,2N7002,Package_TO_SOT_SMD:SOT-23,B,45.60,30.00,0
R12,1k,,Resistor_SMD:R_0402_1005Metric,B,42.60,29.60,90
R13,100k,,Resistor_SMD:R_0402_1005Metric,B,42.60,32.20,90
D4,1N4148W,1N4148W,Diode_SMD:D_SOD-123,B,45.60,26.80,0
R14,1k,,Resistor_SMD:R_0402_1005Metric,F,34.00,4.80,90
D3,RED,,LED_SMD:LED_0603_1608Metric,F,34.00,2.00,90
J11,microSD,104031-0811,Connector_Card:microSD_HC_Molex_104031-0811,B,59.00,20.00,90
C21,100n,,Capacitor_SMD:C_0402_1005Metric,B,49.60,18.00,90
C22,10u,,Capacitor_SMD:C_0805_2012Metric,B,49.60,21.40,90
C23,100n,,Capacitor_SMD:C_0402_1005Metric,F,66.90,21.10,90
R11,0R,,Resistor_SMD:R_0402_1005Metric,B,49.60,15.00,90
TP9,SWDIO,,TestPoint:TestPoint_Pad_D1.5mm,B,23.60,32.20,0
TP10,SWCLK,,TestPoint:TestPoint_Pad_D1.5mm,B,26.10,32.20,0
TP11,NRST,,TestPoint:TestPoint_Pad_D1.5mm,B,28.60,32.20,0
TP12,GND,,TestPoint:TestPoint_Pad_D1.5mm,B,31.10,32.20,0
TP13,+3V3,,TestPoint:TestPoint_Pad_D1.5mm,B,33.60,32.20,0
U7,REF3125,REF3125AIDBZR,Package_TO_SOT_SMD:SOT-23,B,59.90,29.40,0
C24,100n,,Capacitor_SMD:C_0402_1005Metric,F,57.40,30.70,90
C25,1u,,Capacitor_SMD:C_0402_1005Metric,B,57.00,28.50,0

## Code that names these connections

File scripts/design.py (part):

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J1_NAMES = {
    1: 'ETH_A_P', 3: 'ETH_A_N', 5: 'ETH_B_P', 7: 'ETH_B_N', 17: 'ETH_L1', 19: 'ETH_L2',
    21: 'VIN', 23: 'USB1_VBUS', 25: 'USB1_D_P', 27: 'USB1_D_N', 29: 'USB1_ID', 31: 'GND',
    33: 'UART1_TX/PA9', 35: 'UART1_RX/PA10', 37: 'UART1_RTS/PI14', 39: 'UART1_CTS/PI15',
    41: 'VIN', 43: 'I2C1_SDA/PB7', 45: 'I2C1_SCL/PB6', 47: 'GND', 49: 'CAN1_TX/PH13',
    51: 'CAN1_RX/PB8', 53: 'VSYS', 55: 'SDC_CLK/PD6', 57: 'SDC_CMD/PD7', 59: 'SDC_D0/PB14',
    61: 'SDC_D1/PB15', 63: 'SDC_D2/PB3', 65: 'SDC_D3/PB4', 73: 'RESET', 75: 'SWDIO/PA13',
    77: 'SWCK/PA14', 79: 'SWO/PB3',
    10: 'DSI_D1_P', 12: 'DSI_D1_N', 14: 'DSI_D0_P', 16: 'DSI_D0_N', 18: 'DSI_CK_P',
    20: 'DSI_CK_N', 22: 'GND', 26: 'USB0_D_P/PA12', 28: 'USB0_D_N/PA11', 32: 'VIN',
    34: 'UART0_TX/PA0', 36: 'UART0_RX/PI9', 38: 'UART0_RTS/PI10', 40: 'UART0_CTS/PI13',
    42: 'GND', 44: 'I2C0_SDA/PH8', 46: 'I2C0_SCL/PH7', 48: 'VIN', 54: 'GND',
    56: 'I2S_MCK/PD3', 58: 'I2S_WS/PB9', 60: 'I2S_DI/PI2', 62: 'I2S_DO/PI3', 64: 'VSYS',
    66: 'DMIC_CK/PE2', 68: 'DMIC_D0/PB2', 72: 'V_SDCARD',
}
J2_NAMES = {
    1: 'FORCE_BOOTLOADER', 3: 'BOOT_SOURCE/PI8', 5: 'POWER_ON_REQ', 7: 'COINCELL',
    23: '+3V3', 25: 'UART3_TX/PJ8', 27: 'UART3_RX/PJ9', 33: 'GND', 43: '+3V3',
    45: 'I2C2_SDA/PH12', 47: 'I2C2_SCL/PH11', 49: 'SAI_CK/PI5', 51: 'SAI_FS/PI7',
    53: 'SAI_D0/PI6', 57: 'GND', 59: 'PWM0/PA8', 61: 'PWM1/PC6', 63: 'PWM2/PC7',
    65: 'PWM3/PG7', 67: 'PWM4/PJ11', 69: '+3V3', 71: 'ADC_VREF_P', 73: 'A0/PA0_C',
    75: 'A1/PA1_C', 77: 'A2/PC2_C', 79: 'A3/PC3_C',
    2: 'CAM_D7/PI7', 4: 'CAM_D6/PI6', 6: 'CAM_D5/PI4', 8: 'CAM_D4/PH14', 10: 'CAM_D3/PH12',
    12: 'CAM_D2/PH11', 14: 'CAM_D1/PH10', 16: 'CAM_D0/PH9', 18: 'CAM_VS/PI5',
    20: 'CAM_CLK/PA6', 22: 'CAM_HS/PA4', 24: 'GND', 26: 'UART2_TX/PG14', 28: 'UART2_RX/PG9',
    34: '+3V3', 36: 'SPI1_CS/PI0', 38: 'SPI1_CK/PI1', 40: 'SPI1_CIPO/PC2',
    42: 'SPI1_COPI/PC3', 44: 'GND', 46: 'GPIO0/PC13', 48: 'GPIO1/PC15', 50: 'GPIO2/PD4',
    52: 'GPIO3/PD5', 54: 'GPIO4/PE3', 56: 'GPIO5/PG3', 58: 'GPIO6/PG10', 60: 'PWM5/PK1',
    62: 'PWM6/PH15', 64: 'PWM7/PJ7', 66: 'PWM8/PJ10', 68: 'PWM9/PH6', 70: 'GND',
    72: 'ADC_VREF_N', 74: 'A4/PC2', 76: 'A5/PC3', 78: 'A6/PA4', 80: 'A7/PA6',
}

# ---------------------------------------------------------------- H7 connector net use
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    25: 'UART3_TX', 27: 'UART3_RX', 26: 'UART2_TX', 28: 'UART2_RX',
    36: 'IMU_CS', 38: 'SPI1_SCK', 40: 'SPI1_CIPO', 42: 'SPI1_COPI',   # the MCU's SPI2 (AF5)
    50: 'IMU_INT', 52: 'LED_STATUS',
    # Motors: M1 PK1 = TIM1_CH1, M2 PJ11 = TIM1_CH2, M3 PC6 = TIM3_CH1, M4 PC7 = TIM3_CH2 - no complementary
    # channels, DMA on both timers: DShot and bidirectional DShot on all four.
    60: 'M1', 67: 'M2', 61: 'M3', 63: 'M4',
    59: 'ESC_TLM',                                   # PA8 = UART7_RX (AF11): ESC telemetry on its own UART
    # LED strip on PJ10 = TIM8_CH2 (has DMA, so WS2812 works; TIM12 has none on the H7). S6 PH15 = TIM8_CH3N
    # shares TIM8 with it (second LED string or GPIO when the LEDs run). S5 PH6 = TIM12_CH1 (servo PWM).
    # Buzzer PJ7 = GPIO for an active buzzer (its TIM8_CH2N is the LED channel's complement).
    66: 'LED_STRIP', 68: 'S5', 62: 'S6', 64: 'BUZZER',
    71: 'ADC_VREF',                                  # VREF+ from U7 (module only pulls it up weakly, 100k)
    78: 'VBAT_SENSE', 80: 'CURR_SENSE',              # PA4 / PA6: plain ADC pins, not the analog-only PA0_C / PA1_C
}

R0402 = 'Resistor_SMD:R_0402_1005Metric'
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      ('6', 'GND'), ('7', 'RESV'), ('8', 'VDD'), ('9', 'INT2/FSYNC'), ('10', 'RESV'),
      ('11', 'RESV'), ('12', 'AP_CS'), ('13', 'AP_SCLK'), ('14', 'AP_SDI')],
     {1: 'SPI1_CIPO', 4: 'IMU_INT', 5: '+3V3_SENS', 6: 'GND', 7: 'GND', 8: '+3V3_SENS',
      12: 'IMU_CS', 13: 'SPI1_SCK', 14: 'SPI1_COPI'}, 'F', 34.0, 20.0, 0, 'ICM-45686')   # TDK, pin-compatible with ICM-42688-P; JLC 'normal' assembly
# R0.4 cost pass kept it: every cheaper IMU at JLCPCB (ICM-42670-P, BMI270, ICM-42607, MPU-6500, ...) is flagged
# 'processing difficult' (componentProductType 2).  The ICM-42670-P fits these pads unchanged if that ever changes.
two(B, 'C11', 'C', '100n', C0402, '+3V3_SENS', 'GND', 'F', 30.6, 19.2)
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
